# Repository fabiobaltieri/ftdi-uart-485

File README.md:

USB to UART/485 Interface
=========================

This project is a simple USB UART/485 interface based on the FTDI FT232
controller chip.

The board feature two LEDs for bus activity, a 2x3 2.54mm strip with TTL UART
signals and a 485 transceiver with a 8P8C connettor compatible with both
generic 8P8C connectors and Neutrik Ethercon connectors.

License
-------

This program is free software: you can redistribute it and/or modify
it under the terms of the GNU General Public License as published by
the Free Software Foundation, either version 3 of the License, or
(at your option) any later version.

Contents
--------

    COPYING     text version of the GPL
    README      this file
    hardware/   source directory for the hardware design files

Firmware
--------

No firmware is needed for this design. FTDI drivers are already available on
most GNU/Linux distributions.

Hardware
--------

All hardware files (schematic, layout and libraries) are in CadSoft Eagle
format.

The PCB is designed to work at 3.3V for UART signal/485 levels, but can be
easily modified to work at 5V by bypassing the 3.3V linear regulator and
mounting a standard 5V 485 transceiver.

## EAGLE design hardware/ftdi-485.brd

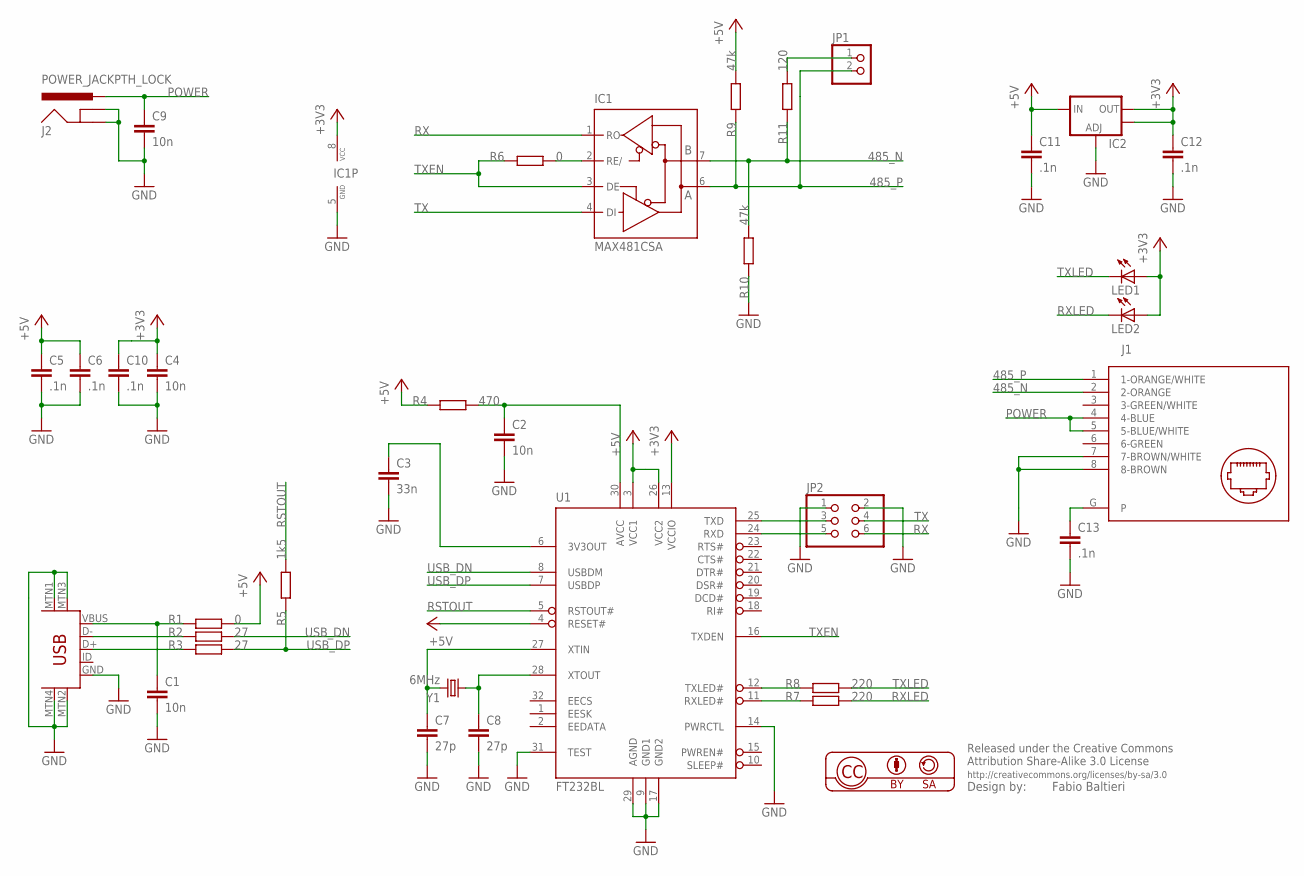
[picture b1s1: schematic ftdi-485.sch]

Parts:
C1, C2, C4, C9: 10n; C0805
C3: 33n; C0805
C5, C6, C10, C11, C12, C13: .1n; C0805
C7, C8: 27p; C0805
IC1: MAX481CSA; SO08
IC2: V_REG_LM1117SOT223; SOT223
J1: NE8FAH
J2: POWER_JACKPTH_LOCK; POWER_JACK_PTH_LOCK
JP1: PINHD-1X2; 1X02
JP2: PINHD-2X3; 2X03
LED1, LED2: LEDCHIP-LED0805; CHIP-LED0805
R1, R6: 0; R0603
R2, R3: 27; R0603
R4: 470; R0603
R5: 1k5; R0603
R7, R8: 220; R0603
R9, R10: 47k; R0603
R11: 120; R0603
U1: FT232BL; LQFP32
U$2: USB-MINIB-5PIN; USB-MINIB
Y1: 6MHz; HC49U-V

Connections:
485_N: IC1.7 (B), J1.2 (2-ORANGE), R10.2, R11.1
485_P: IC1.6 (A), J1.1 (1-ORANGE/WHITE), JP1.2, R9.1
+3V3: C4.1, C10.1, C12.1, IC1.8 (VCC), IC2.2 (OUT), IC2.4 (OUT), LED1.A, LED2.A, U1.13 (VCCIO)
+5V: C5.1, C6.1, C11.1, IC2.3 (IN), R1.2, R4.1, R9.2, U1.3 (VCC1), U1.4 (RESET#), U1.26 (VCC2)
GND: C1.2, C2.2, C3.2, C4.2, C5.2, C6.2, C7.2, C8.2, C9.2, C10.2, C11.2, C12.2, C13.2, IC1.5 (GND), IC2.1 (ADJ), J1.7 (7-BROWN/WHITE), J1.8 (8-BROWN), J2.GND, J2.GNDBREAK, JP2.1, JP2.2, R10.1, U1.9 (GND1), U1.14 (PWRCTL), U1.17 (GND2), U1.29 (AGND), U1.31 (TEST), U$2.GND, U$2.MTN1 (MTN2), U$2.MTN2 (MTN3), U$2.MTN3 (MTN1), U$2.MTN4
unnamed: C1.1, R1.1, U$2.VBUS
unnamed: R2.1, U$2.D-
unnamed: R3.1, U$2.D+
unnamed: R8.1, U1.12 (TXLED#)
unnamed: C2.1, R4.2, U1.30 (AVCC)
unnamed: C3.1, U1.6 (3V3OUT)
unnamed: C7.1, U1.27 (XTIN), Y1.2
unnamed: C8.1, U1.28 (XTOUT), Y1.1
unnamed: R7.1, U1.11 (RXLED#)
unnamed: IC1.2 (RE/), R6.2
unnamed: JP1.1, R11.2
unnamed: JP2.5, U1.24 (RXD)
unnamed: JP2.3, U1.25 (TXD)
unnamed: C13.1, J1.G
POWER: C9.1, J1.4 (4-BLUE), J1.5 (5-BLUE/WHITE), J2.PWR
RSTOUT: R5.2, U1.5 (RSTOUT#)
RX: IC1.1 (RO), JP2.6
RXLED: LED2.C, R7.2
TX: IC1.4 (DI), JP2.4
TXEN: IC1.3 (DE), R6.1, U1.16 (TXDEN)
TXLED: LED1.C, R8.2
USB_DN: R2.2, U1.8 (USBDM)
USB_DP: R3.2, R5.1, U1.7 (USBDP)

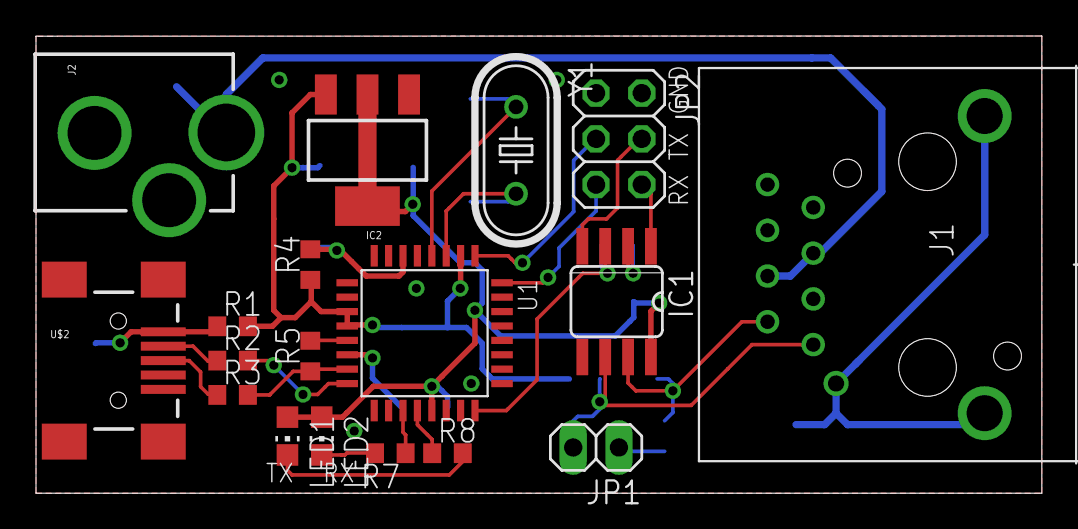
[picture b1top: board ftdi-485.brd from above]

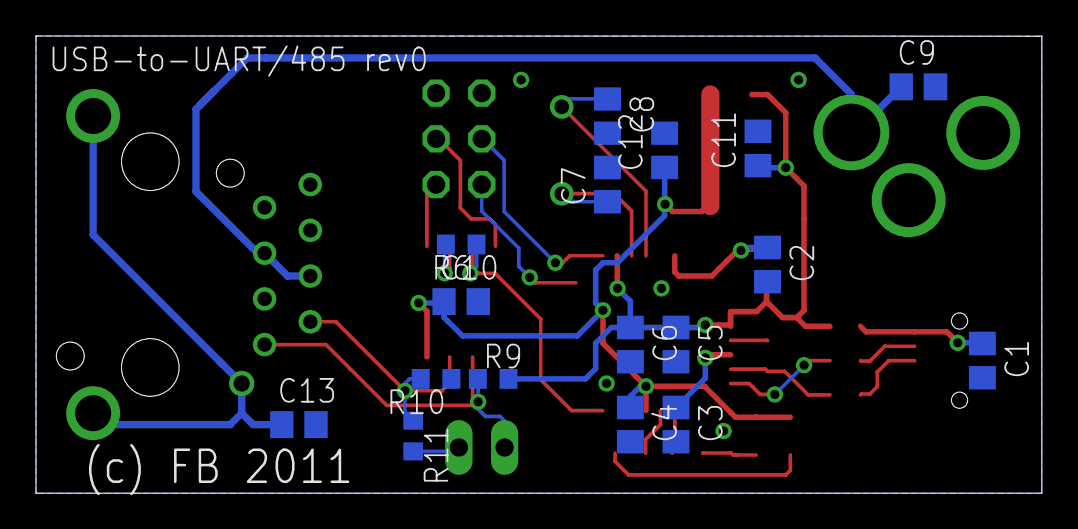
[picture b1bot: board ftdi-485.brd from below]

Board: 2 copper layers, 55.9 x 25.4 mm, 35 parts (17 on the bottom side), 28 nets.

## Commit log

2011-11-17 initial import of README and license files
2011-11-17 initial import of hardware files
2011-11-17 hardware: add schematic in pdf version
2011-11-20 hardware: add CC BY-SA license
2012-01-23 hardware: convert files to eagle v6 version (xml)
2012-01-24 hardware: cosmetic changes
